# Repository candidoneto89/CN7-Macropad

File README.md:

# CN7 Macropad

**CN7 Macropad** is a custom-built mechanical keyboard, packing features:
- 9 programmable keys made for shortcuts;
- layer-indication LEDs;
- rotary encoder for commands such as media control and CAD features like zoom, etc;
- RGB addressable LEDs for underglow and individual key-lightning;

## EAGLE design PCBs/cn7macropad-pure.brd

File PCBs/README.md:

# BOM
|Parts                                                  |Value           |Package                |Qty      |
|-------------------------------------------------------|----------------|-----------------------|---------|
|C1                                                     |10uF            |0603-CAP               |1        |
|C2, C3, C4, C5, C6                                     |1.0uF           |0603-CAP               |5        |
|C7, C8                                                 |22pF            |0603-CAP               |2        |
|C9, C10, C11, C12, C13, C14, C15, C16, <br>C17, C18, C19, C20, C21, C22, C23, C24, C25|0.1uf|0603|17       |
|D1                                                     |3A/10V/280mV    |SOD-323                |1        |
|D12, D13                                               |                |SOD-523                |2        |
|D2, D3, D4, D14, D15                                   |                |LED-0603               |5        |
|D5, D6, D7, D8, D9, D10, D11                           |                |SOD-523                |7        |
|J2                                                     |USB-C Connector |GCT_USB4105_REVA       |1        |
|LED_1, LED_2, LED_3, LED_4, LED_5, LED_6, LED_7, LED_8, LED_9|SK6812-MINI-E|SK6812-MINI-E       |9        |
|LED_10                                                 |WS2812B5050     |WS2812B                |1        |
|LED_11, LED_12, LED_13, LED_14, LED_15, LED_16, LED_17 |WS2812B5050     |WS2812B                |7        |
|R1, R2                                                 |5.1k            |R0603                  |2        |
|R10, R11, R12, R14, R15                                |200             |R0603                  |5        |
|R3, R4                                                 |22              |R0603                  |2        |
|R5, R6, R7, R8, R13                                    |10k             |R0603                  |5        |
|R9                                                     |500             |R0603                  |1        |
|S2                                                     |KMR621NGLFS     |SW_KMR621NGLFS         |1        |
|SW10                                                   |EC11B-V-T       |EC11B-V                |1        |
|SW1, SW2, SW3, SW4, SW5, SW6, SW7, SW8, SW9            |KAILH           |HOT-SWAP SOCKET        |9        |
|U$1                                                    |PTC-FUSE        |PTC1206                |1        |
|U1                                                     |ATMEGA32U4      |TQFP44                 |1        |
|Y2                                                     |CRYSTAL         |SMD-3.2X2.5MM          |1        |

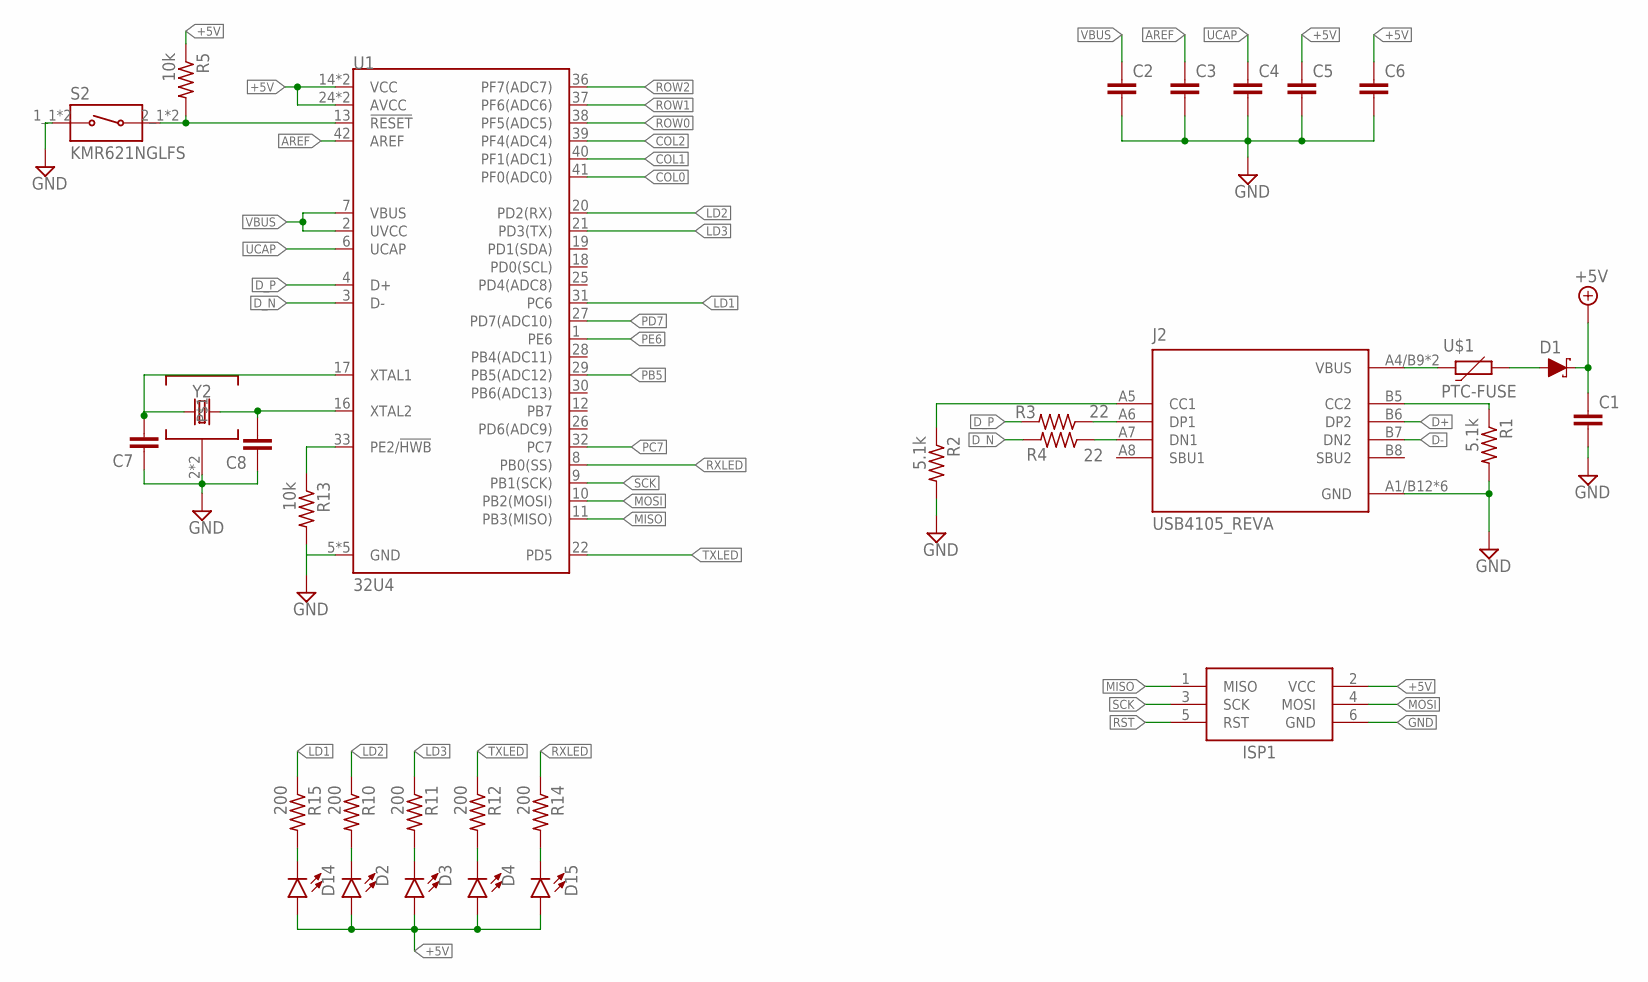
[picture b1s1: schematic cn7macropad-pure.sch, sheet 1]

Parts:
C1: 10uF; 0603
C2, C3, C4, C5, C6: 1.0uF; 0603
C7, C8: 22pF; 0603
D1: 3A/10V/280mV; SOD-323
D2, D3, D4, D14, D15: LED0603; LED-0603
ISP1: AVRISP-6; AVRISP
J2: USB4105_REVA; GCT_USB4105_REVA
R1, R2: 5.1k; R0603
R3, R4: 22; R0603
R5, R13: 10k; R0603
R10, R11, R12, R14, R15: 200; R0603
S2: KMR621NGLFS; SW_KMR621NGLFS
U1: 32U4; TQFP44
U$1: PTC-FUSE; PTC1206
Y2: CRYSTALSMD-3.2X2.5; CRYSTAL-SMD-3.2X2.5MM

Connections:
+5V: C1.1, C5.1, C6.1, D1.C, D2.A, D3.A, D4.A, D14.A, D15.A, ISP1.2 (VCC), R5.1, U1.14 (VCC), U1.24 (AVCC), U1.34 (VCC), U1.44 (AVCC); also elsewhere on the board
AREF: C3.1, U1.42 (AREF)
CC1: J2.A5 (CC1), R2.1
CC2: J2.B5 (CC2), R1.1
COL0: U1.41 (PF0(ADC0)); also elsewhere on the board
COL1: U1.40 (PF1(ADC1)); also elsewhere on the board
COL2: U1.39 (PF4(ADC4)); also elsewhere on the board
D+: J2.A6 (DP1), J2.B6 (DP2), R3.1
D-: J2.A7 (DN1), J2.B7 (DN2), R4.1
D_N: R4.2, U1.3 (D-)
D_P: R3.2, U1.4 (D+)
GND: C1.2, C2.2, C3.2, C4.2, C5.2, C6.2, C7.1, C8.1, ISP1.6 (GND), J2.A1/B12 (GND), J2.B1/A12 (GND), J2.G1 (GND), J2.G2 (GND), J2.G3 (GND), J2.G4 (GND), R1.2, R2.2, R13.2, S2.1_1 (1), S2.1_2 (1), U1.5 (GND), U1.15 (GND), U1.23 (GND), U1.35 (GND), U1.43 (GND), Y2.2, Y2.4; also elsewhere on the board
LD1: R15.1, U1.31 (PC6)
LD2: R10.1, U1.20 (PD2(RX))
LD3: R11.1, U1.21 (PD3(TX))
MISO: ISP1.1 (MISO), U1.11 (PB3(MISO)); also elsewhere on the board
MOSI: ISP1.4 (MOSI), U1.10 (PB2(MOSI))
unnamed: R13.1, U1.33 (PE2/!HWB)
unnamed: D15.C, R14.2
unnamed: D14.C, R15.2
unnamed: D1.A, U$1.2
unnamed: C7.2, U1.17 (XTAL1), Y2.1
unnamed: C8.2, U1.16 (XTAL2), Y2.3 (2)
unnamed: D2.C, R10.2
unnamed: D3.C, R11.2
unnamed: D4.C, R12.2
PB5: U1.29 (PB5(ADC12)); also elsewhere on the board
PC7: U1.32 (PC7); also elsewhere on the board
PD7: U1.27 (PD7(ADC10)); also elsewhere on the board
PE6: U1.1 (PE6)
ROW0: U1.38 (PF5(ADC5)); also elsewhere on the board
ROW1: U1.37 (PF6(ADC6)); also elsewhere on the board
ROW2: U1.36 (PF7(ADC7)); also elsewhere on the board
RST: ISP1.5 (RST), R5.2, S2.2_1 (2), S2.2_2 (2), U1.13 (!RESET)
RXLED: R14.1, U1.8 (PB0(SS))
SCK: ISP1.3 (SCK), U1.9 (PB1(SCK))
TXLED: R12.1, U1.22 (PD5)
UCAP: C4.1, U1.6 (UCAP)
VBUS: C2.1, J2.A4/B9 (VBUS), J2.B4/A9 (VBUS), U1.2 (UVCC), U1.7 (VBUS), U$1.1

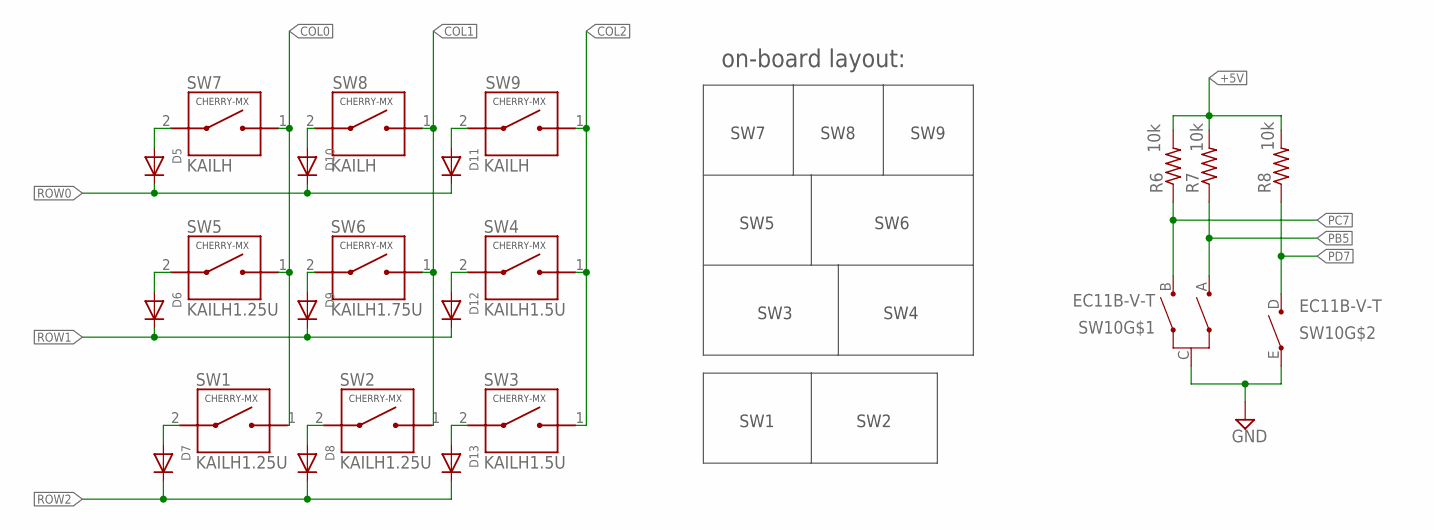
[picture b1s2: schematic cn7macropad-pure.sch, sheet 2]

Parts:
D5, D6, D7, D8, D9, D10, D11: DIODE; SOD-523
D12, D13: DIODESOD-523; SOD-523
R6, R7, R8: 10k; R0603
SW1, SW2, SW5: KAILH1.25U; SWITCH_SOCKET-1.25U
SW3, SW4: KAILH1.5U; SWITCH_SOCKET-1.5U
SW6: KAILH1.75U; SWITCH_SOCKET-1.75U
SW7, SW8, SW9: KAILH; SWITCH_SOCKET-1U
SW10: EC11B-V-T; EC11B-V

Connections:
+5V: R6.2, R7.2, R8.2; also elsewhere on the board
COL0: SW1.1 (2), SW5.1 (2), SW7.1 (2); also elsewhere on the board
COL1: SW2.1 (2), SW6.1 (2), SW8.1 (2); also elsewhere on the board
COL2: SW3.1 (2), SW4.1 (2), SW9.1 (2); also elsewhere on the board
GND: SW10.C, SW10.E; also elsewhere on the board
unnamed: D5.A, SW7.2 (1)
unnamed: D6.A, SW5.2 (1)
unnamed: D9.A, SW6.2 (1)
unnamed: D10.A, SW8.2 (1)
unnamed: D7.A, SW1.2 (1)
unnamed: D8.A, SW2.2 (1)
unnamed: D13.A, SW3.2 (1)
unnamed: D12.A, SW4.2 (1)
unnamed: D11.A, SW9.2 (1)
PB5: R7.1, SW10.A; also elsewhere on the board
PC7: R6.1, SW10.B; also elsewhere on the board
PD7: R8.1, SW10.D; also elsewhere on the board
ROW0: D5.K (C), D10.K (C), D11.K (C); also elsewhere on the board
ROW1: D6.K (C), D9.K (C), D12.K (C); also elsewhere on the board
ROW2: D7.K (C), D8.K (C), D13.K (C); also elsewhere on the board

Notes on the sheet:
on-board layout:
SW1
SW2
SW3
SW4
SW6
SW5
SW7
SW8
SW9

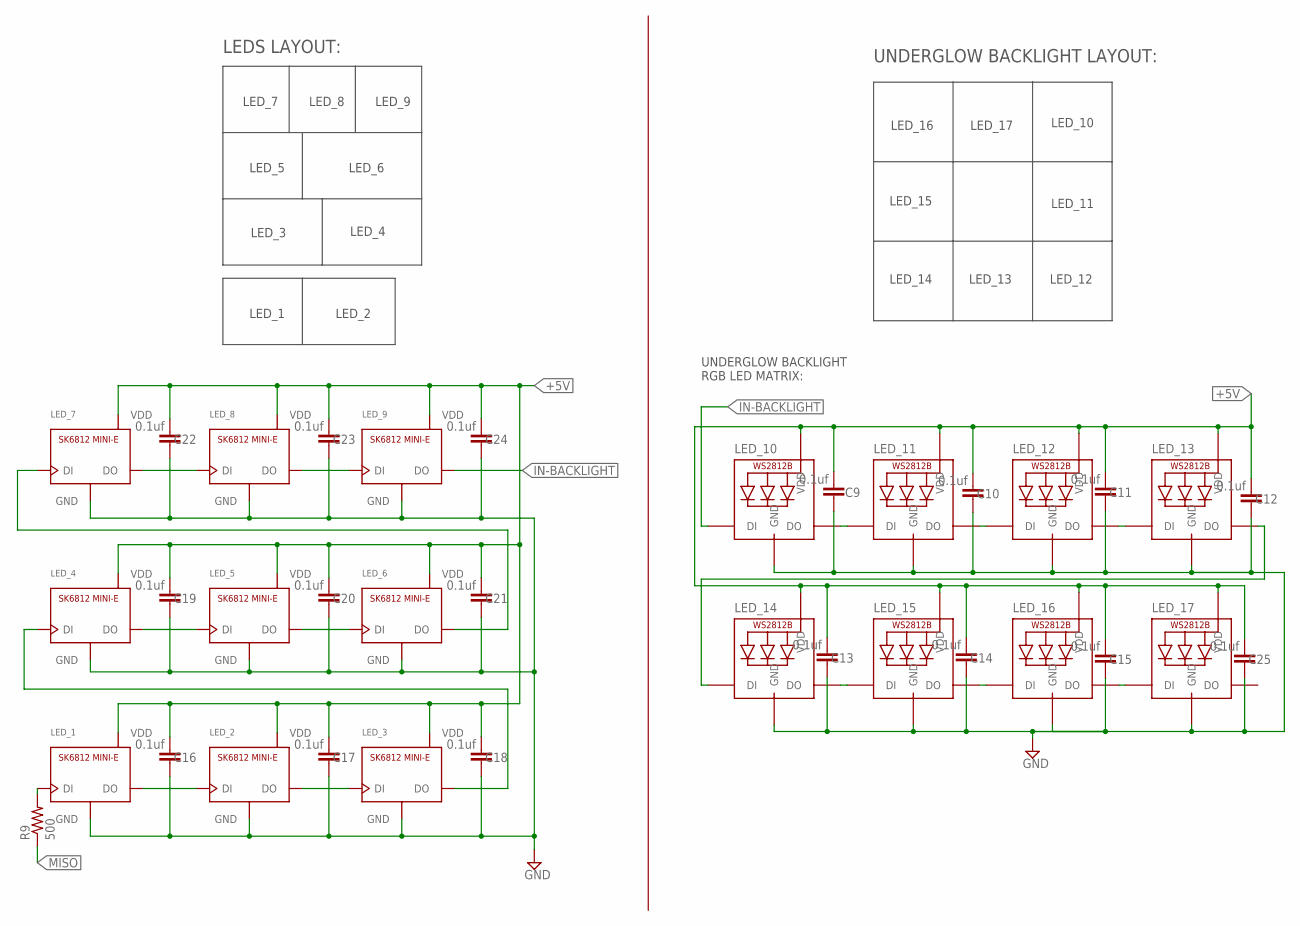
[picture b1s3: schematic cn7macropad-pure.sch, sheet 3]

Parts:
C9, C10, C11, C12, C13, C14, C15, C16, C17, C18, C19, C20, C21, C22, C23, C24, C25: 0.1uf; 0603
LED_1, LED_2, LED_3, LED_4, LED_5, LED_6, LED_7, LED_8, LED_9: SK6812-MINI-ESW; SK6812-MINI-E
LED_10, LED_11, LED_12, LED_13, LED_14, LED_15, LED_16, LED_17: WS2812B5050; WS2812B
R9: 500; R0603

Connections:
+5V: C9.2, C10.2, C11.2, C12.2, C13.2, C14.2, C15.2, C16.2, C17.2, C18.2, C19.2, C20.2, C21.2, C22.2, C23.2, C24.2, C25.2, LED_1.1-VDD (VDD), LED_2.1-VDD (VDD), LED_3.1-VDD (VDD), LED_4.1-VDD (VDD), LED_5.1-VDD (VDD), LED_6.1-VDD (VDD), LED_7.1-VDD (VDD), LED_8.1-VDD (VDD), LED_9.1-VDD (VDD), LED_10.1-VDD (VDD), LED_11.1-VDD (VDD), LED_12.1-VDD (VDD), LED_13.1-VDD (VDD), LED_14.1-VDD (VDD), LED_15.1-VDD (VDD), LED_16.1-VDD (VDD), LED_17.1-VDD (VDD); also elsewhere on the board
GND: C9.1, C10.1, C11.1, C12.1, C13.1, C14.1, C15.1, C16.1, C17.1, C18.1, C19.1, C20.1, C21.1, C22.1, C23.1, C24.1, C25.1, LED_1.3-GND (GND), LED_2.3-GND (GND), LED_3.3-GND (GND), LED_4.3-GND (GND), LED_5.3-GND (GND), LED_6.3-GND (GND), LED_7.3-GND (GND), LED_8.3-GND (GND), LED_9.3-GND (GND), LED_10.3-GND (GND), LED_11.3-GND (GND), LED_12.3-GND (GND), LED_13.3-GND (GND), LED_14.3-GND (GND), LED_15.3-GND (GND), LED_16.3-GND (GND), LED_17.3-GND (GND); also elsewhere on the board
IN-BACKLIGHT: LED_9.2-DOUT (DO), LED_10.4-DIN (DI)
MISO: R9.1; also elsewhere on the board
unnamed: LED_1.2-DOUT (DO), LED_2.4-DIN (DI)
unnamed: LED_2.2-DOUT (DO), LED_3.4-DIN (DI)
unnamed: LED_1.4-DIN (DI), R9.2
unnamed: LED_3.2-DOUT (DO), LED_4.4-DIN (DI)
unnamed: LED_4.2-DOUT (DO), LED_5.4-DIN (DI)
unnamed: LED_5.2-DOUT (DO), LED_6.4-DIN (DI)
unnamed: LED_6.2-DOUT (DO), LED_7.4-DIN (DI)
unnamed: LED_7.2-DOUT (DO), LED_8.4-DIN (DI)
unnamed: LED_8.2-DOUT (DO), LED_9.4-DIN (DI)
unnamed: LED_10.2-DOUT (DO), LED_11.4-DIN (DI)
unnamed: LED_11.2-DOUT (DO), LED_12.4-DIN (DI)
unnamed: LED_13.2-DOUT (DO), LED_14.4-DIN (DI)
unnamed: LED_14.2-DOUT (DO), LED_15.4-DIN (DI)
unnamed: LED_15.2-DOUT (DO), LED_16.4-DIN (DI)
unnamed: LED_16.2-DOUT (DO), LED_17.4-DIN (DI)
unnamed: LED_12.2-DOUT (DO), LED_13.4-DIN (DI)

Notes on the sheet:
LEDS LAYOUT:
LED_1
LED_2
LED_3
LED_4
LED_6
LED_5
LED_7
LED_8
LED_9
UNDERGLOW BACKLIGHT LAYOUT:
LED_10
LED_11
LED_12
LED_13
LED_14
LED_15
LED_16
UNDERGLOW BACKLIGHT RGB LED MATRIX:
LED_17

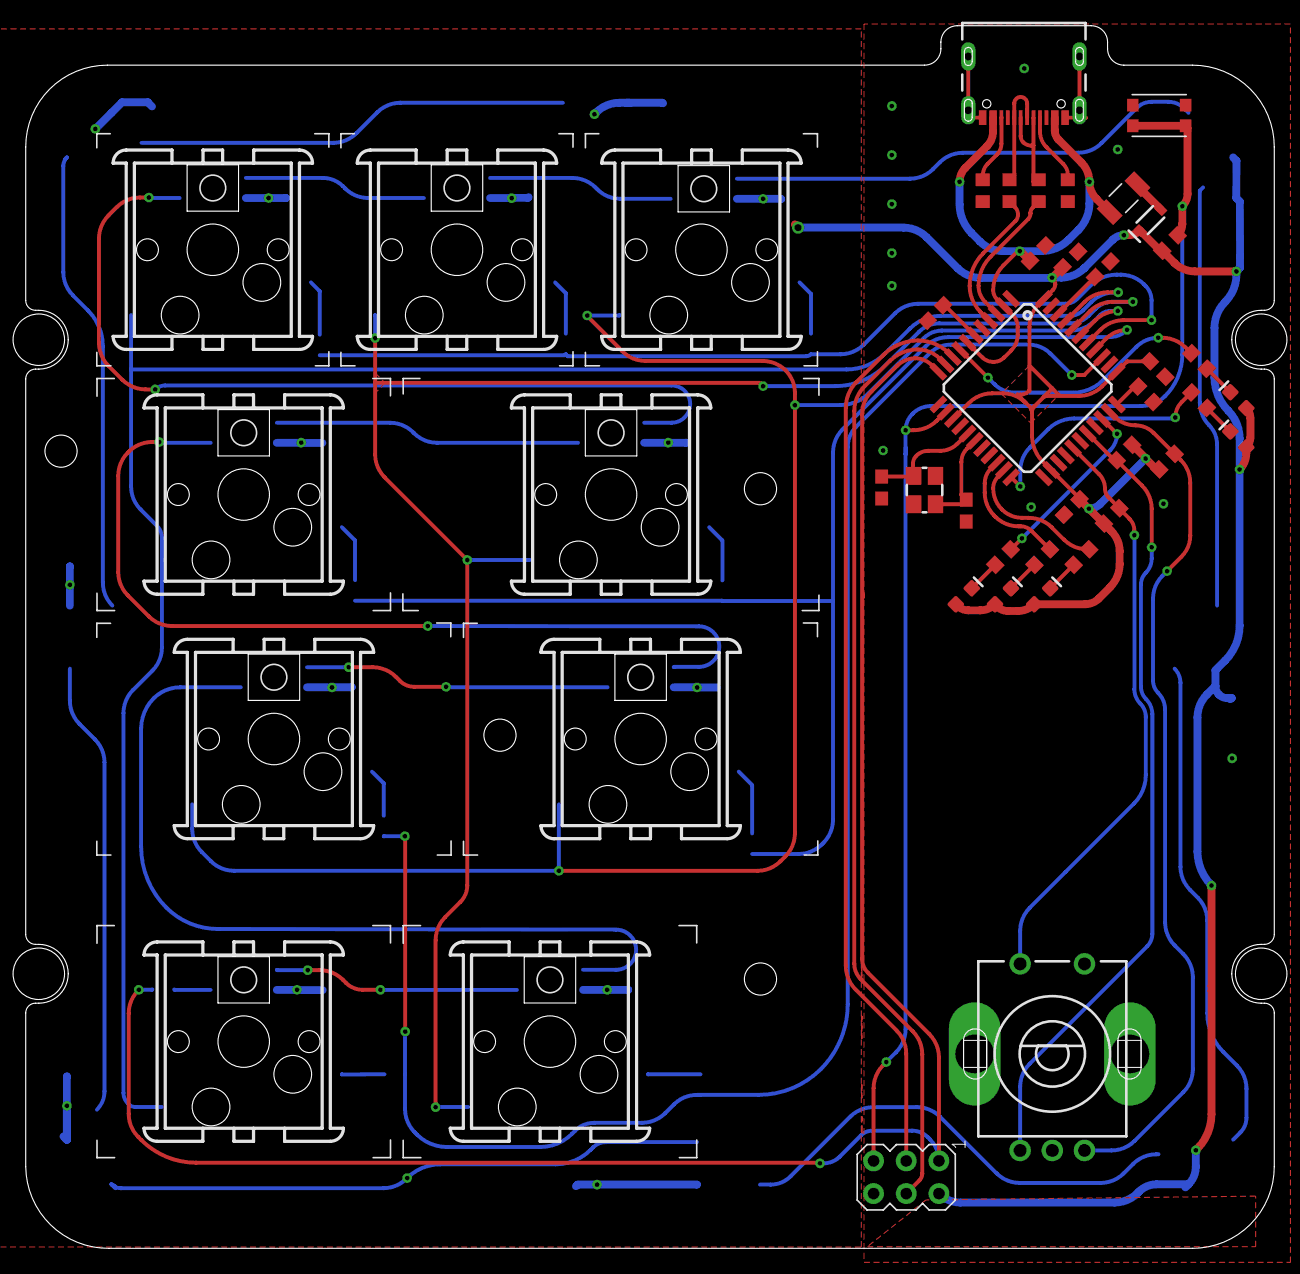
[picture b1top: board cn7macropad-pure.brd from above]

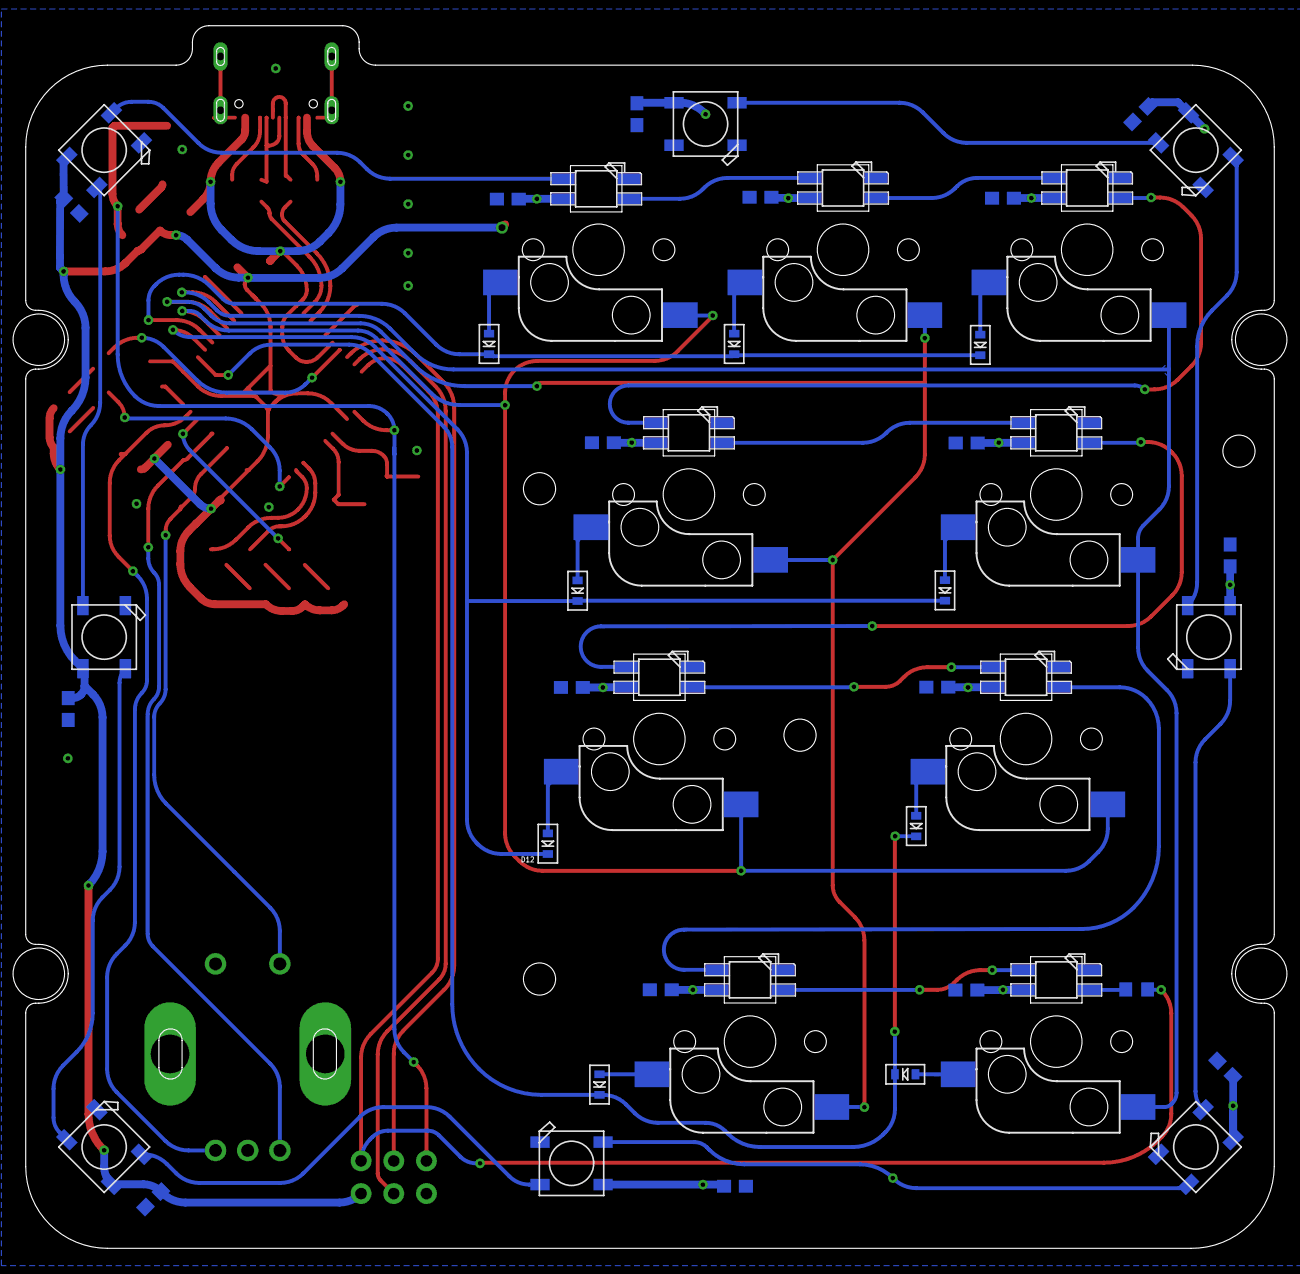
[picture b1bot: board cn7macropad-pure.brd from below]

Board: 2 copper layers, 97.0 x 95.0 mm, 88 parts (35 on the bottom side), 64 nets.

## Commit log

2022-04-13 Primeiro commit
2022-04-13 adding boards
2022-04-13 adding pictures
2022-04-13 firmware
2025-08-22 small improvements on code
2025-09-24 added 3D case files
2025-09-24 3d renders

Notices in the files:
parts and their libraries:
SparkFun-DiscreteSemi: Licensing: Creative Commons ShareAlike 4.0 International - https://creativecommons.org/licenses/by-sa/4.0
